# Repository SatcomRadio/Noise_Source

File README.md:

# Noise source board

This repo consists of a board for making a noise source. 

## Warning! This board is still a work in progress!

It's based on the one made by [Changpuak](https://www.changpuak.ch/electronics/Noise-Source-with-2xGVA82-15dB.php).

It's adapted to work in a enclosure like [this one](https://www.aliexpress.com/item/1005001849603652.html) of size 92x38x31mm to store it.

------------------------

## Bill of materials

```
4x 0805 1 ohm resistor (https://aliexpress.com/item/1005009264768923.html)
2x 0805 100 ohm resistor (https://aliexpress.com/item/1005009264768923.html)
3x 0805 1uF capacitor (https://aliexpress.com/item/1005005000107445.html)
2x 0805 10uF capacitor (https://aliexpress.com/item/1005005000107445.html)
2x GVA-82+ Mini-Circuits Amplifier (https://aliexpress.com/item/1005008544947091.html)
2x TCBT-14+ Mini-Circuits Bias Tee (https://aliexpress.com/item/1005007678313474.html)
2x PAT-3+ Mini-Circuits 3 dB Attenuator (https://aliexpress.com/item/1005008375039512.html)
1x SMA PCB 1.6mm long connector (https://aliexpress.com/item/1005007424915378.html)
1x 12V barrel jack connector (https://aliexpress.com/item/1005008726787916.html)
1x MC7805CDTG 5v voltage regulator (https://aliexpress.com/item/1005007905517148.html)
1x Storage box (https://www.aliexpress.com/item/1005001849603652.html)
```

------------------------

Schema:

------------------------

## Ordering the PCB:

Download the Gerber file from this repo and order it a jlcpcb with the default options.  
The only option I've changed is to remove the manufacture code mark

#### Please make sure to visit the [satcom radio website](https://satcomradio.github.io/) for more information

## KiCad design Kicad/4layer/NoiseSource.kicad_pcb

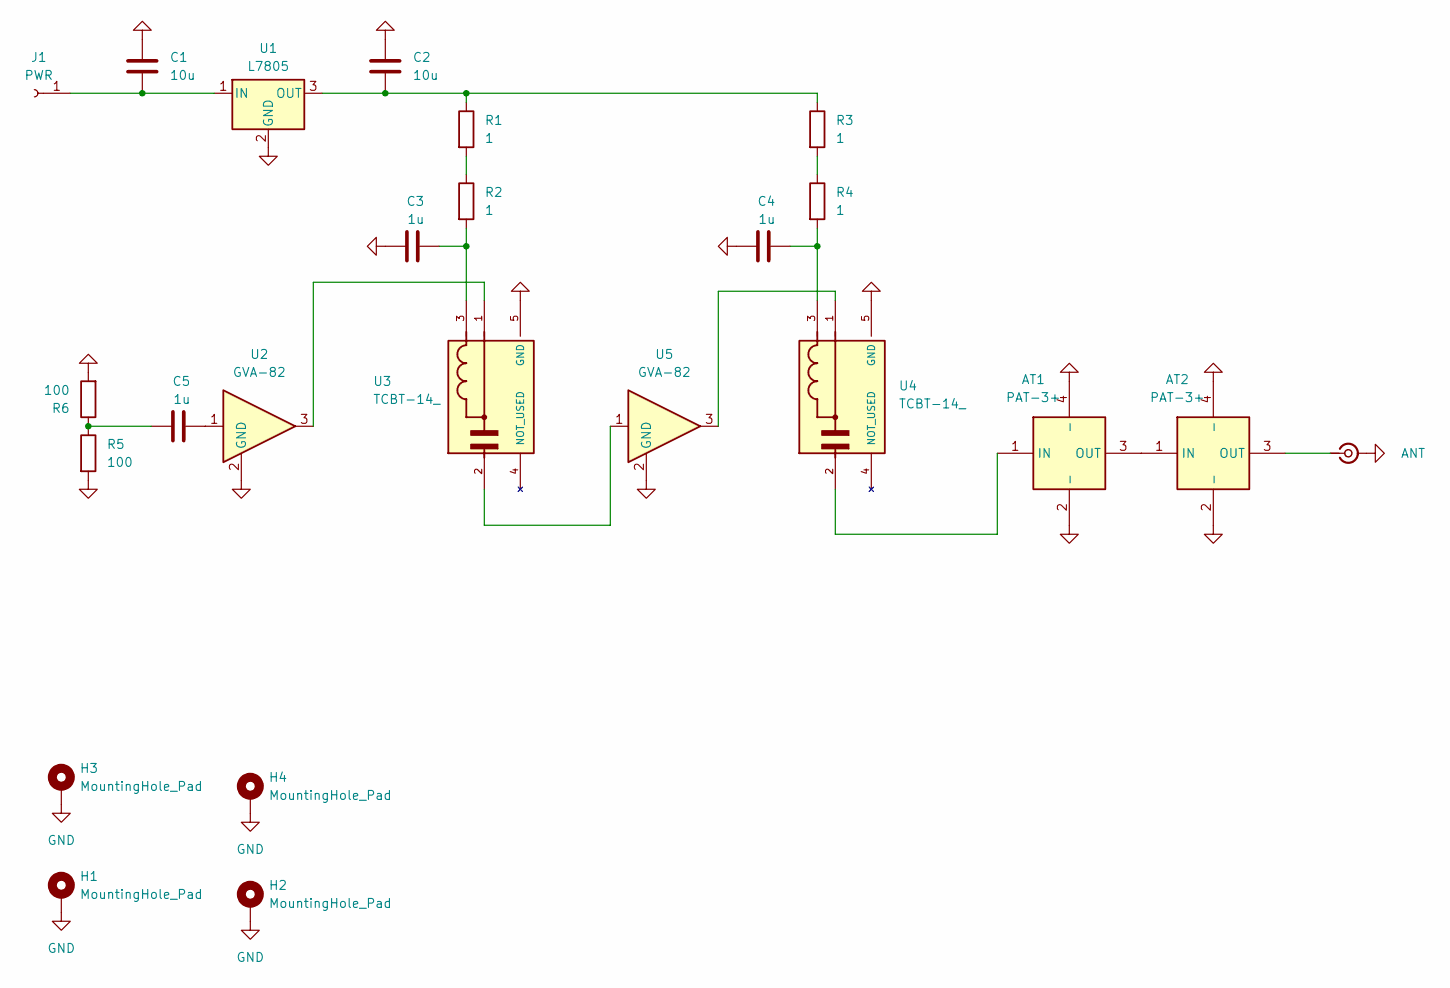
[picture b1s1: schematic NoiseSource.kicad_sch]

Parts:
AT1, AT2: PAT-3+; PAT3; Mouser Part Number 139-PAT-3+
C1, C2: 10u; C_0805_2012Metric_Pad1.18x1.45mm_HandSolder
C3, C4, C5: 1u; C_0805_2012Metric_Pad1.18x1.45mm_HandSolder
H1, H2, H3, H4: MountingHole_Pad; MountingHole_3.2mm_M3_Pad_Via
J1: PWR; TestPoint_Pad_D2.0mm
J2: ANT; SMA_Edge
R1, R2, R3, R4: 1; R_0805_2012Metric_Pad1.20x1.40mm_HandSolder
R5, R6: 100; R_0805_2012Metric_Pad1.20x1.40mm_HandSolder
U1: L7805; TO-252-2
U2, U5: GVA-82; SOT-89-3_VIAS
U3, U4: TCBT-14_; IC_TCBT-14_; PARTREV C

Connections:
GND: AT1.2 (-), AT1.4 (-), AT2.2 (-), AT2.4 (-), C1.2, C2.2, C3.2, C4.2, H1.1, H2.1, H3.1, H4.1, J2.2 (Ext), R5.2, R6.2, U1.2 (GND), U2.2 (GND), U3.5 (GND), U4.5 (GND), U5.2 (GND)
unnamed: AT1.1 (IN), U4.2
unnamed: AT1.3 (OUT), AT2.1 (IN)
unnamed: AT2.3 (OUT), J2.1 (In)
unnamed: C3.1, R2.2, U3.3
unnamed: C4.1, R4.2, U4.3
unnamed: C5.1, U2.1
unnamed: C5.2, R5.1, R6.1
unnamed: C1.1, J1.1, U1.1 (IN)
unnamed: R1.2, R2.1
unnamed: R3.2, R4.1
unnamed: C2.1, R1.1, R3.1, U1.3 (OUT)
unnamed: U2.3, U3.1
unnamed: U3.2, U5.1
unnamed: U4.1, U5.3

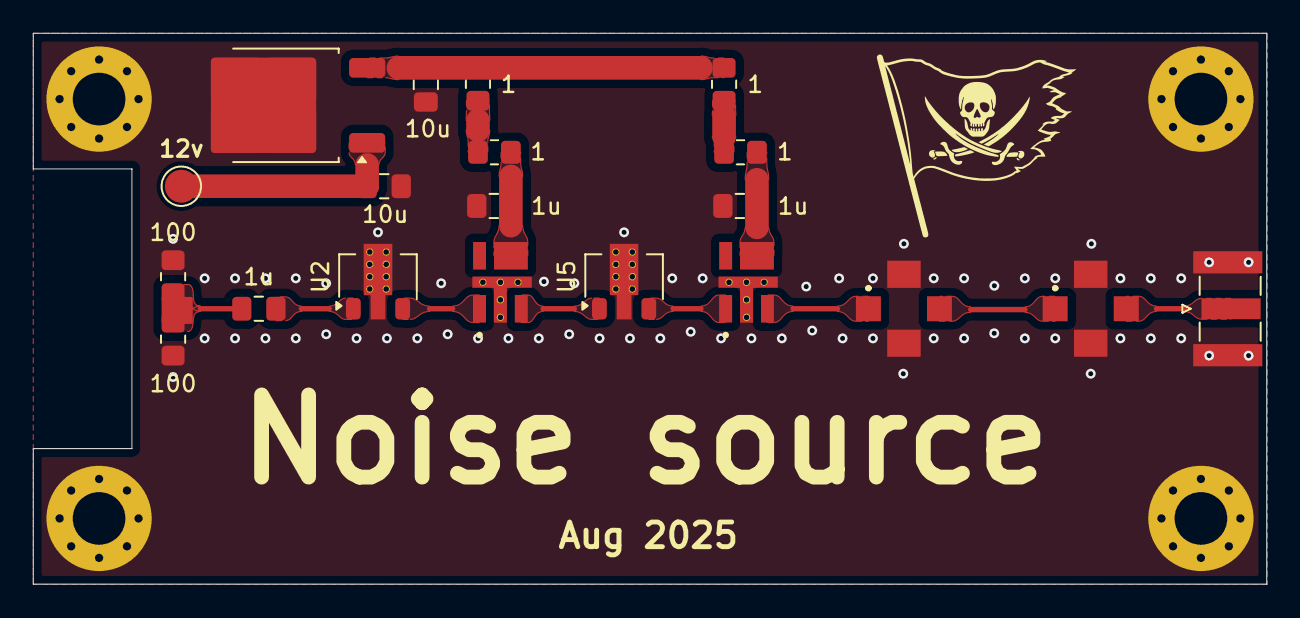
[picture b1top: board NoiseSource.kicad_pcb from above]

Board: 4 copper layers, 75.0 x 33.5 mm, 24 parts (0 on the bottom side), 15 nets.

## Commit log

2025-07-29 Initial upload
2025-07-29 Fix img
2025-07-29 Update render and footprints
2025-07-29 Readme update
2025-07-31 update gitignore
2025-07-31 Added 2 and 4 layer version
